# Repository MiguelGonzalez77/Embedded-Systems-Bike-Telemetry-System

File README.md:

# ECE445L Final Lab

A Bike Telemetry system that can track parameters such as heartrate, distance, speed, etc. It uses a ARM Cortex-M (TM4C123) microcontroller with reed switches, an LCD ST7735 display screen, and heart rate monitor. This was done using C and ARM Cortex-M Assembly as well as including a custom PCB and schematics done in KiCAD.

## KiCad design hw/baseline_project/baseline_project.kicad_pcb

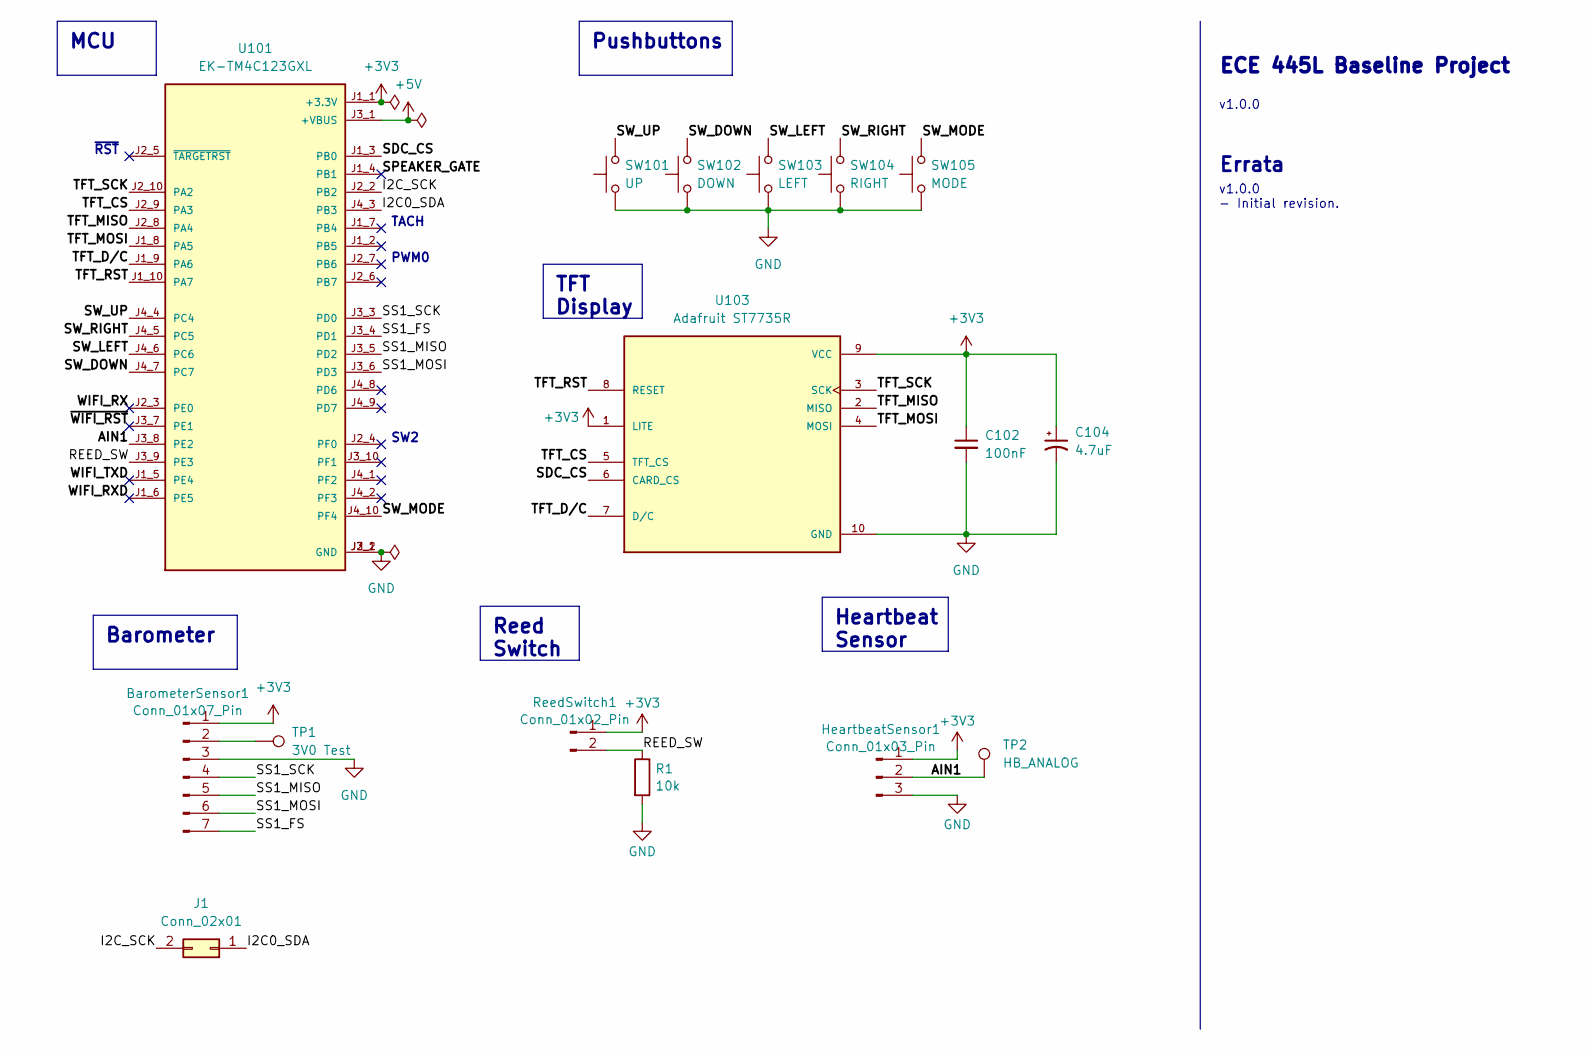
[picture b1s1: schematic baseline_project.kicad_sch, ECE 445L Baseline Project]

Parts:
BarometerSensor1: Conn_01x07_Pin; PinHeader_1x07_P2.54mm_Vertical
C102: 100nF; C_Axial_L5.1mm_D3.1mm_P15.00mm_Horizontal
C104: 4.7uF; CP_Axial_L10.0mm_D4.5mm_P15.00mm_Horizontal
HeartbeatSensor1: Conn_01x03_Pin; PinHeader_1x03_P2.54mm_Vertical
J1: Conn_02x01; PinHeader_1x02_P2.54mm_Vertical
R1: 10k; R_Axial_DIN0204_L3.6mm_D1.6mm_P2.54mm_Vertical
ReedSwitch1: Conn_01x02_Pin; PinHeader_1x02_P2.54mm_Vertical
SW101: UP; SW_PUSH_6mm
SW102: DOWN; SW_PUSH_6mm
SW103: LEFT; SW_PUSH_6mm
SW104: RIGHT; SW_PUSH_6mm
SW105: MODE; SW_PUSH_6mm
TP1: 3V0 Test; TestPoint_Pad_D1.0mm
TP2: HB_ANALOG; TestPoint_Pad_D1.0mm
U101: EK-TM4C123GXL; ti_EKTM4C123GXL
U103: Adafruit ST7735R; adafruit_st7735r

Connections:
+3V3: BarometerSensor1.1, C102.1, C104.1, HeartbeatSensor1.1, ReedSwitch1.1, U101.J1_1 (+3.3V), U103.1 (LITE), U103.9 (VCC); also elsewhere on the board
+5V: U101.J3_1 (+VBUS)
/AIN1: HeartbeatSensor1.2, TP2.1, U101.J3_8 (PE2); also elsewhere on the board
/I2C0_SDA: J1.1, U101.J4_3 (PB3)
/I2C_SCK: J1.2, U101.J2_2 (PB2)
/REED_SW: R1.1, ReedSwitch1.2, U101.J3_9 (PE3)
/SDC_CS: U101.J1_3 (PB0), U103.6 (CARD_CS)
/SPEAKER_GATE: U101.J1_4 (PB1)
/SS1_FS: BarometerSensor1.7, U101.J3_4 (PD1)
/SS1_MISO: BarometerSensor1.5, U101.J3_5 (PD2)
/SS1_MOSI: BarometerSensor1.6, U101.J3_6 (PD3)
/SS1_SCK: BarometerSensor1.4, U101.J3_3 (PD0)
/SW_DOWN: SW102.2, U101.J4_7 (PC7)
/SW_LEFT: SW103.2, U101.J4_6 (PC6)
/SW_MODE: SW105.2, U101.J4_10 (PF4)
/SW_RIGHT: SW104.2, U101.J4_5 (PC5)
/SW_UP: SW101.2, U101.J4_4 (PC4)
/TFT_CS: U101.J2_9 (PA3), U103.5 (TFT_CS)
/TFT_D/C: U101.J1_9 (PA6), U103.7 (D/C)
/TFT_MISO: U101.J2_8 (PA4), U103.2 (MISO)
/TFT_MOSI: U101.J1_8 (PA5), U103.4 (MOSI)
/TFT_RST: U101.J1_10 (PA7), U103.8 (RESET)
/TFT_SCK: U101.J2_10 (PA2), U103.3 (SCK)
/WIFI_RX: U101.J2_3 (PE0)
/WIFI_RXD: U101.J1_6 (PE5)
/WIFI_TXD: U101.J1_5 (PE4)
/~WIFI_RST: U101.J3_7 (PE1)
GND: BarometerSensor1.3, C102.2, C104.2, HeartbeatSensor1.3, R1.2, SW101.1, SW102.1, SW103.1, SW104.1, SW105.1, U101.J2_1 (GND), U101.J3_2 (GND), U103.10 (GND); also elsewhere on the board
unnamed: BarometerSensor1.2, TP1.1

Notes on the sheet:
MCU
Heartbeat Sensor
Pushbuttons
TFT Display
Barometer
Reed Switch
v1.0.0 - Initial revision.
~{RST}
PWM0
TACH
ECE 445L Baseline Project
v1.0.0
Errata
SW2

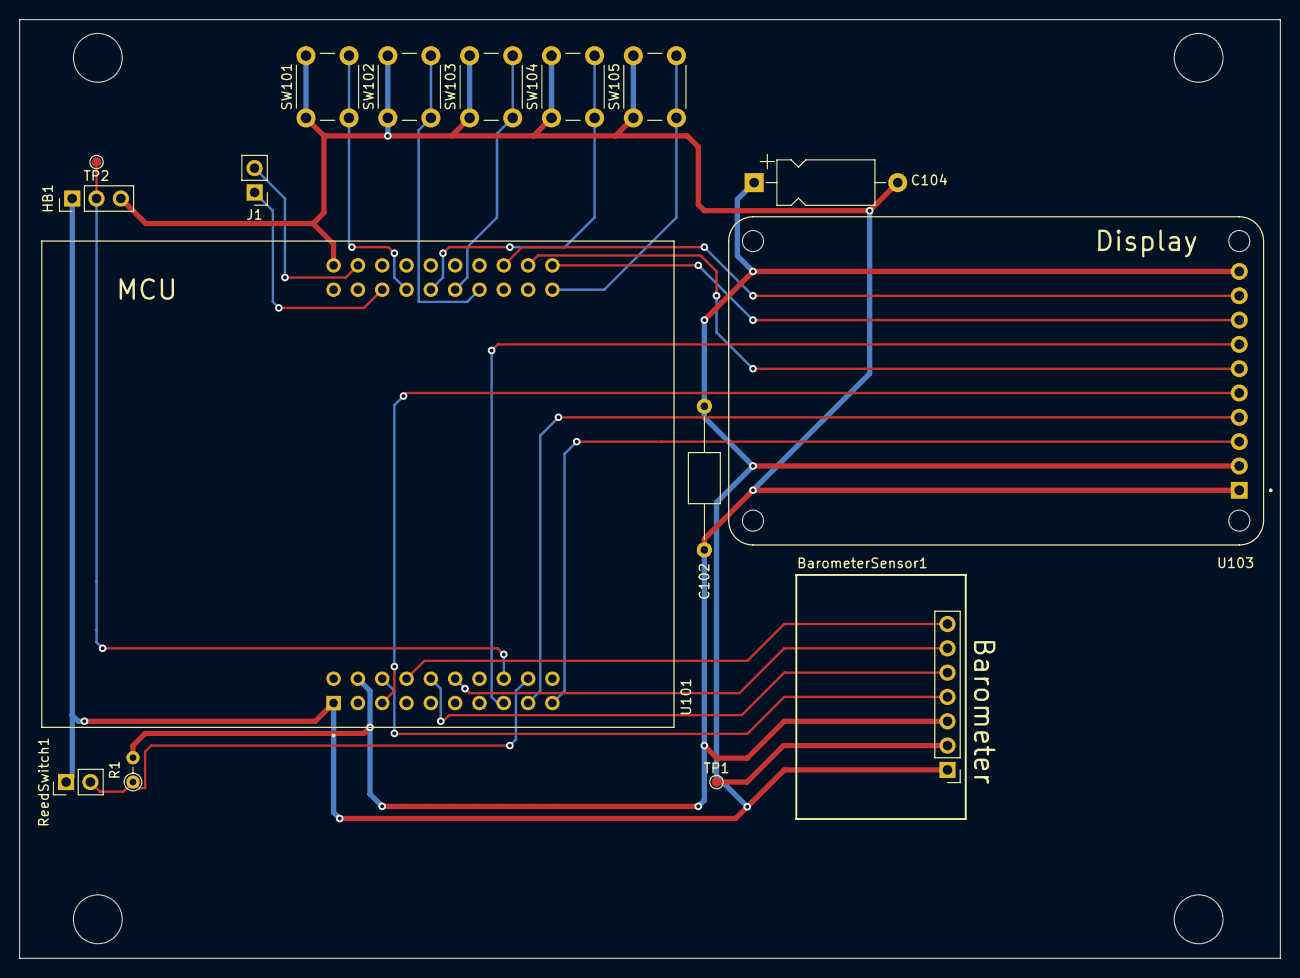
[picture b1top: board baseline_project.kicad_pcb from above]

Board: 2 copper layers, 131.7 x 98.1 mm, 16 parts (0 on the bottom side), 23 nets.

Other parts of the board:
HB1: Conn_01x03_Pin; PinHeader_1x03_P2.54mm_Vertical

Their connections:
+3V3: HB1.1; also elsewhere on the board
/AIN1: HB1.2; also elsewhere on the board
GND: HB1.3; also elsewhere on the board

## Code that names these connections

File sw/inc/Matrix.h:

// Matrix.h
// Runs on  LM4F120/TM4C123
// Provide functions that initialize GPIO ports and SysTick 
// Use periodic polling
// Daniel Valvano
// August 11, 2014

/* This example accompanies the book
   "Embedded Systems: Real Time Interfacing to Arm Cortex M Microcontrollers",
   ISBN: 978-1463590154, Jonathan Valvano, copyright (c) 2015

   Example 5.4, Figure 5.18, Program 5.13

Copyright 2015 by Jonathan W. Valvano, valvano@mail.utexas.edu
    You may use, edit, run or distribute this file
    as long as the above copyright notice remains
 THIS SOFTWARE IS PROVIDED "AS IS".  NO WARRANTIES, WHETHER EXPRESS, IMPLIED
 OR STATUTORY, INCLUDING, BUT NOT LIMITED TO, IMPLIED WARRANTIES OF
 MERCHANTABILITY AND FITNESS FOR A PARTICULAR PURPOSE APPLY TO THIS SOFTWARE.
 VALVANO SHALL NOT, IN ANY CIRCUMSTANCES, BE LIABLE FOR SPECIAL, INCIDENTAL,
 OR CONSEQUENTIAL DAMAGES, FOR ANY REASON WHATSOEVER.
 For more information about my classes, my research, and my books, see
 http://users.ece.utexas.edu/~valvano/
 */
#pragma once

// PA5 connected to column 3 (keypad pin 4) using 10K pull-up
// PA4 connected to column 2 (keypad pin 3) using 10K pull-up
// PA3 connected to column 1 (keypad pin 2) using 10K pull-up
// PA2 connected to column 0 (keypad pin 1) using 10K pull-up
// PD3 connected to row 3 (keypad pin 8)
// PD2 connected to row 2 (keypad pin 7)
// PD1 connected to row 1 (keypad pin 6) (remove R9, R10)
// PD0 connected to row 0 (keypad pin 5) (remove R9, R10)

// [1] [2] [3] [A]
// [4] [5] [6] [B]
// [7] [8] [9] [C]
// [*] [0] [#] [D]
// Pin1 . . . . . . . . Pin8
// Pin 1 -> Column 0 (column starting with 1)
// Pin 2 -> Column 1 (column starting with 2)
// Pin 3 -> Column 2 (column starting with 3)
// Pin 4 -> Column 3 (column starting with A)
// Pin 5 -> Row 0 (row starting with 1)
// Pin 6 -> Row 1 (row starting with 4)
// Pin 7 -> Row 2 (row starting with 7)
// Pin 8 -> Row 3 (row starting with *)


// Initialization of Matrix keypad
void Matrix_Init(void);
       
// input ASCII character from keypad
// spin if Fifo is empty
char Matrix_InChar(void);

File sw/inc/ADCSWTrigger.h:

// ADCSWTrigger.h
// Runs on TM4C123
// Provide functions that initialize ADC0 SS3 to be triggered by
// software and trigger a conversion, wait for it to finish,
// and return the result.
// Daniel Valvano
// January 15, 2020
#pragma once

/* This example accompanies the book
   "Embedded Systems: Real Time Interfacing to Arm Cortex M Microcontrollers",
   ISBN: 978-1463590154, Jonathan Valvano, copyright (c) 2020

 Copyright 2020 by Jonathan W. Valvano, valvano@mail.utexas.edu
    You may use, edit, run or distribute this file
    as long as the above copyright notice remains
 THIS SOFTWARE IS PROVIDED "AS IS".  NO WARRANTIES, WHETHER EXPRESS, IMPLIED
 OR STATUTORY, INCLUDING, BUT NOT LIMITED TO, IMPLIED WARRANTIES OF
 MERCHANTABILITY AND FITNESS FOR A PARTICULAR PURPOSE APPLY TO THIS SOFTWARE.
 VALVANO SHALL NOT, IN ANY CIRCUMSTANCES, BE LIABLE FOR SPECIAL, INCIDENTAL,
 OR CONSEQUENTIAL DAMAGES, FOR ANY REASON WHATSOEVER.
 For more information about my classes, my research, and my books, see
 http://users.ece.utexas.edu/~valvano/
 */

// There are many choices to make when using the ADC, and many
// different combinations of settings will all do basically the
// same thing.  For simplicity, this function makes some choices
// for you.  When calling this function, be sure that it does
// not conflict with any other software that may be running on
// the microcontroller.  Particularly, ADC0 sample sequencer 3
// is used here because it only takes one sample, and only one
// sample is absolutely needed.  Sample sequencer 3 generates a
// raw interrupt when the conversion is complete, but it is not
// promoted to a controller interrupt.  Software triggers the
// ADC0 conversion and waits for the conversion to finish.  If
// somewhat precise periodic measurements are required, the
// software trigger can occur in a periodic interrupt.  This
// approach has the advantage of being simple.  However, it does
// not guarantee real-time.
//
// A better approach would be to use a hardware timer to trigger
// the ADC0 conversion independently from software and generate
// an interrupt when the conversion is finished.  Then, the
// software can transfer the conversion result to memory and
// process it after all measurements are complete.

// This initialization function sets up the ADC according to the
// following parameters.  Any parameters not explicitly listed
// below are not modified:
// Max sample rate: <=125,000 samples/second
// Sequencer 0 priority: 1st (highest)
// Sequencer 1 priority: 2nd
// Sequencer 2 priority: 3rd
// Sequencer 3 priority: 4th (lowest)
// SS3 triggering event: software trigger
// SS3 1st sample source: Ain9 (PE4)
// SS3 interrupts: enabled but not promoted to controller
void ADC0_InitSWTriggerSeq3_Ch9(void);

// This initialization function sets up the ADC according to the
// following parameters.  Any parameters not explicitly listed
// below are not modified:
// Max sample rate: <=125,000 samples/second
// Sequencer 0 priority: 1st (highest)
// Sequencer 1 priority: 2nd
// Sequencer 2 priority: 3rd
// Sequencer 3 priority: 4th (lowest)
// SS3 triggering event: software trigger
// SS3 1st sample source: programmable using variable 'channelNum' [0:7]
// SS3 interrupts: enabled but not promoted to controller
void ADC0_InitSWTriggerSeq3(uint32_t channelNum);

// This initialization function sets up the ADC according to the
// following parameters.  Any parameters not explicitly listed
// below are not modified:
// Max sample rate: <=125,000 samples/second
// Sequencer 0 priority: 1st (highest)
// Sequencer 1 priority: 2nd
// Sequencer 2 priority: 3rd
// Sequencer 3 priority: 4th (lowest)
// SS3 triggering event: always trigger
// SS3 1st sample source: programmable using variable 'channelNum' [0:11]
// SS3 interrupts: enabled but not promoted to controller
void ADC0_InitAllTriggerSeq3(uint32_t channelNum);

// This initialization function sets up the ADC according to the
// following parameters.  Any parameters not explicitly listed
// below are not modified:
// Max sample rate: <=125,000 samples/second
// Sequencer 0 priority: 1st (highest)
// Sequencer 1 priority: 2nd
// Sequencer 2 priority: 3rd
// Sequencer 3 priority: 4th (lowest)
// SS3 triggering event: always trigger
// SS3 1st sample source: programmable using variable 'channelNum' [0:11]
// SS3 interrupts: enabled but not promoted to controller
void ADC0_InitAllTriggerSeq3(uint32_t channelNum);
// PD0 is AIN7
void ADC0_InitSWTriggerSeq3_Ch7(void);

//------------ADC0_InSeq3------------
// Busy-wait Analog to digital conversion
// Input: none
// Output: 12-bit result of ADC conversion
uint32_t ADC0_InSeq3(void);

// Initializes ADC8 and ADC9 sampling
// 125k max sampling
// SS2 triggering event: software trigger, busy-wait sampling
// SS2 1st sample source: Ain9 (PE4)
// SS2 2nd sample source: Ain8 (PE5)
// SS2 interrupts: enabled after 2nd sample but not promoted to controller
void ADC_Init89(void);

//------------ADC_In89------------
// Busy-wait Analog to digital conversion
// Input: none
// Output: two 12-bit result of ADC conversions
// Samples ADC8 and ADC9 
// 125k max sampling
// software trigger, busy-wait sampling
// data returned by reference
// data[0] is ADC8 (PE5) 0 to 4095
// data[1] is ADC9 (PE4) 0 to 4095
void ADC_In89(uint32_t data[2]);



// SS2 triggering event: software trigger, busy-wait sampling
// SS2 1st sample source: AIN6 (PD1)
// SS2 2nd sample source: AIN5 (PD2)
// SS2 3st sample source: AIN4 (PD3)
// SS2 interrupts: enabled after 3rd sample but not promoted to controller
// 'task' is a pointer to a user function called in SS2 interrupt
// the user function has three parameters that get the x-, y-, and
// z-values from the accelerometer passed by value
void ADC0_InitSWTriggerSeq2(void(*task)(uint32_t x, uint32_t y, uint32_t z));

//------------ADC0_InSeq2------------
// Busy-wait Analog to digital conversion initiates SS2 and
// calls the user function provided in the initialization with
// the results of the conversion in the parameters.
// UserTask2(AIN6, AIN5, AIN4);
// Input: none
// Output: none
// Samples ADC6, ADC5, and ADC4
// 125k max sampling
// software trigger, busy-wait sampling
void ADC0_InSeq2(void);

// This initialization function sets up the ADC according to the
// following parameters.  Any parameters not explicitly listed
// below are not modified:
// Max sample rate: <=125,000 samples/second
// Sequencer 0 priority: 1st (highest)
// Sequencer 1 priority: 2nd
// Sequencer 2 priority: 3rd
// Sequencer 3 priority: 4th (lowest)
// SS3 triggering event: software trigger
// SS3 1st sample source: internal temperature
// SS3 interrupts: enabled but not promoted to controller
void ADC0_InitSWTriggerSeq3_InternalTemperature(void);

//------------ADC0_InSeq3_InternalTemperature------------
// Busy-wait Analog to digital conversion
// Input: none
// Output: 12-bit result of ADC conversion
uint32_t ADC0_InSeq3_InternalTemperature(void);

// Initializes ADC0(PE3), ADC1(PE2), ADC2(PE1) and ADC3(PE0) sampling
// 125k max sampling
// SS2 triggering event: software trigger, busy-wait sampling
// SS2 1st sample source: Ain0 (PE3)
// SS2 2nd sample source: Ain1 (PE2)
// SS2 3rd sample source: Ain2 (PE1)
// SS2 4th sample source: Ain3 (PE0)
// SS2 interrupts: enabled after 4th sample but not promoted to controller
void ADC_Init3210(void);

//------------ADC_In3210------------
// Busy-wait Analog to digital conversion
// Input: none
// Output: four 12-bit result of ADC conversions
// Samples ADC0(PE3), ADC1(PE2), ADC2(PE1) and ADC3(PE0) 
// 125k max sampling
// software trigger, busy-wait sampling
// data returned by reference
// data[0] is ADC3 (PE0) 0 to 4095
// data[1] is ADC2 (PE1) 0 to 4095
// data[2] is ADC1 (PE2) 0 to 4095
// data[3] is ADC0 (PE3) 0 to 4095
void ADC_In3210(uint32_t data[4]);

/* Calibration data
distance measured from front of the sensor to the wall                
d(cm) 1/d    bL     al     aR   bR  adcSample d (0.01cm)  error
10    0.100  2813  2830  2820  2830  2823.25  1006        0.06
15    0.067  1935  1976  1986  1978  1968.75  1482       -0.18
20    0.050  1520  1500  1520  1550  1522.5   1966       -0.34
30    0.033  1040  1096  1028   933  1024.25  3099        0.99
  
      adcSample = 26813/d+159      2681300    
      d = 26813/(adcSample-159)      -159    
*/

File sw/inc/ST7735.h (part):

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// ST7735
// Backlight (pin 10) connected to +3.3 V
// MISO (pin 9) unconnected
// SCK (pin 8) connected to PA2 (SSI0Clk)
// MOSI (pin 7) connected to PA5 (SSI0Tx)
// TFT_CS (pin 6) connected to PA3 (SSI0Fss)
// CARD_CS (pin 5) unconnected
// Data/Command (pin 4) connected to PA6 (GPIO), high for data, low for command
// RESET (pin 3) connected to PA7 (GPIO)
// VCC (pin 2) connected to +3.3 V
// Gnd (pin 1) connected to ground

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// Silkscreen Label (SDC side up; LCD side down) - Connection
// VCC  - +3.3 V
// GND  - Ground
// !SCL - PA2 Sclk SPI clock from microcontroller to TFT or SDC
// !SDA - PA5 MOSI SPI data from microcontroller to TFT or SDC
// DC   - PA6 TFT data/command
// RES  - PA7 TFT reset
// CS   - PA3 TFT_CS, active low to enable TFT
// *CS  - (NC) SDC_CS, active low to enable SDC
// MISO - (NC) MISO SPI data from SDC to microcontroller
// SDA  � (NC) I2C data for ADXL345 accelerometer
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// Silkscreen Label (SDC side up; LCD side down) - Connection
// VCC  - +3.3 V
// GND  - Ground
// !SCL - PA2 Sclk SPI clock from microcontroller to TFT or SDC
// !SDA - PA5 MOSI SPI data from microcontroller to TFT or SDC
// DC   - PA6 TFT data/command
// RES  - PA7 TFT reset
// CS   - PA3 TFT_CS, active low to enable TFT
// *CS  - (NC) SDC_CS, active low to enable SDC
// MISO - (NC) MISO SPI data from SDC to microcontroller
// X� (NC) analog input X-axis from ADXL335 accelerometer
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// MOSI   (pin 13) SDC, MOSI
// MISO   (pin 12) SDC, MISO
// SCK    (pin 11) SDC, serial clock
// CS     (pin 10) TFT, PA3 (SSI0Fss)
// SCL    (pin 9)  TFT, SCK  PA2 (SSI0Clk)
// SDA    (pin 8)  TFT, MOSI PA5 (SSI0Tx)
// A0     (pin 7)  TFT, Data/Command PA6 (GPIO), high for data, low for command
// RESET  (pin 6)  TFT, to PA7 (GPIO)
// NC     (pins 3,4,5) not connected
// VCC    (pin 2)  connected to +3.3 V
// GND    (pin 1)  connected to ground
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
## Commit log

2025-10-23 added files

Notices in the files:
sw/inc/ST7735.h:
MIT license, all text above must be included in any redistribution
"Embedded Systems: Introduction to ARM Cortex M Microcontrollers",
ISBN: 978-1469998749, Jonathan Valvano, copyright (c) 2020
